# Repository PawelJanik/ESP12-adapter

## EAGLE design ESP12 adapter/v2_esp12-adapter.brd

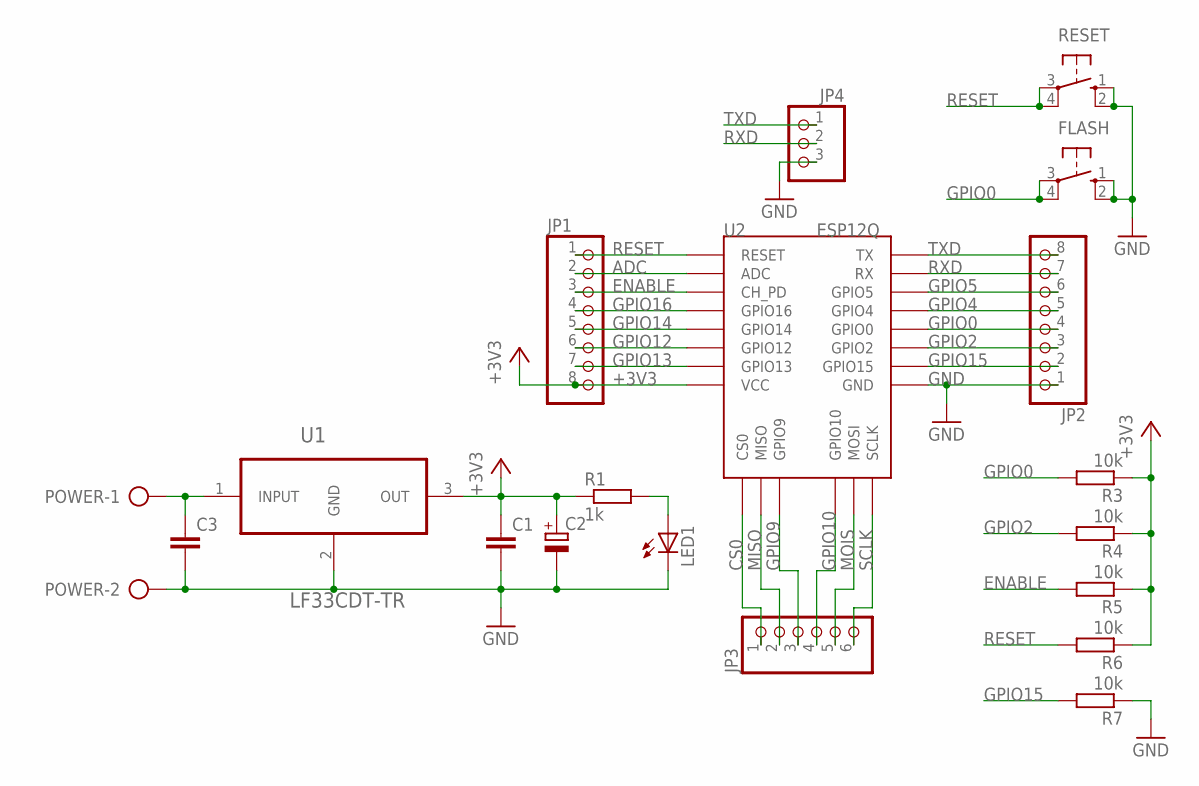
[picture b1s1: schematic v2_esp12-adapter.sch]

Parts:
C1, C3: C-EU025-025X050; C025-025X050
C2: CPOL-EUE2,5-6E; E2,5-6E
FLASH: 10-XX; B3F-10XX
JP1, JP2: PINHD-1X8; 1X08
JP3: PINHD-1X6; 1X06
JP4: PINHD-1X3/90; 1X03/90
LED1: LED5MM
POWER: AK300/2
R1: 1k; R1206
R3, R4, R5, R6, R7: 10k; R1206
RESET: 10-XX; B3F-10XX
U1: LF33CDT-TR; TO228P972X240-3N
U2: ESP12Q

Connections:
+3V3: C1.1, C2.+, JP1.8, R1.1, R3.1, R4.1, R5.1, R6.1, U1.3 (OUT), U2.VCC
ADC: JP1.2, U2.ADC
CS0: JP3.1, U2.CS0
ENABLE: JP1.3, R5.2, U2.CH_PD
GND: C1.2, C2.-, C3.2, FLASH.1 (S), FLASH.2 (S1), JP2.1, JP4.3, LED1.K (C), POWER.2, R7.1, RESET.1 (S), RESET.2 (S1), U1.2 (GND), U2.GND
GPIO0: FLASH.3, FLASH.4 (P1), JP2.4, R3.2, U2.GPIO0
GPIO2: JP2.3, R4.2, U2.GPIO2
GPIO4: JP2.5, U2.GPIO5 (GPIO4)
GPIO5: JP2.6, U2.GPIO4 (GPIO5)
GPIO9: JP3.3, U2.GPIO9
GPIO10: JP3.4, U2.GPIO10
GPIO12: JP1.6, U2.GPIO12
GPIO13: JP1.7, U2.GPIO13
GPIO14: JP1.5, U2.GPIO14
GPIO15: JP2.2, R7.2, U2.GPIO15
GPIO16: JP1.4, U2.GPIO16
MISO: JP3.2, U2.MISO
MOIS: JP3.5, U2.MOSI
unnamed: LED1.A, R1.2
RESET: JP1.1, R6.2, RESET.3, RESET.4 (P1), U2.RESET
RXD: JP2.7, JP4.2, U2.RX
SCLK: JP3.6, U2.SCLK
TXD: JP2.8, JP4.1, U2.TX
V+: C3.1, POWER.1, U1.1 (INPUT)

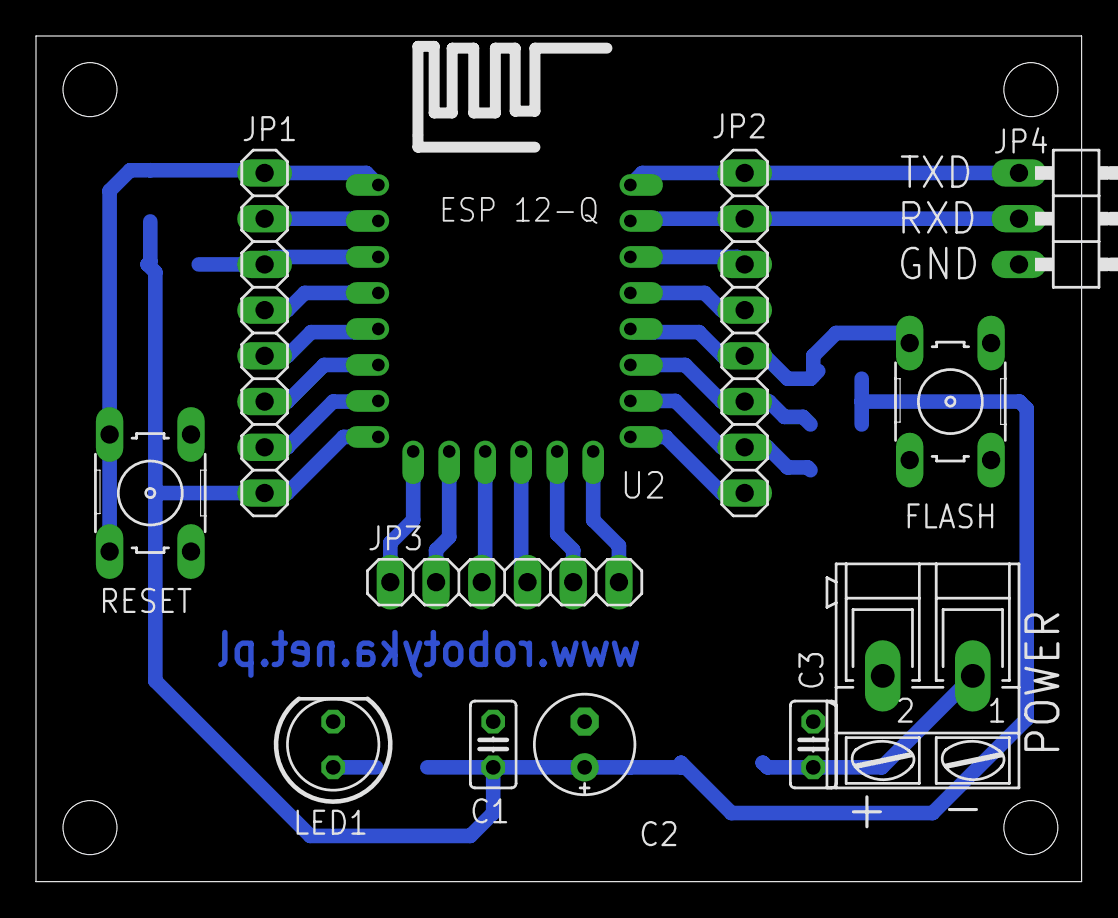
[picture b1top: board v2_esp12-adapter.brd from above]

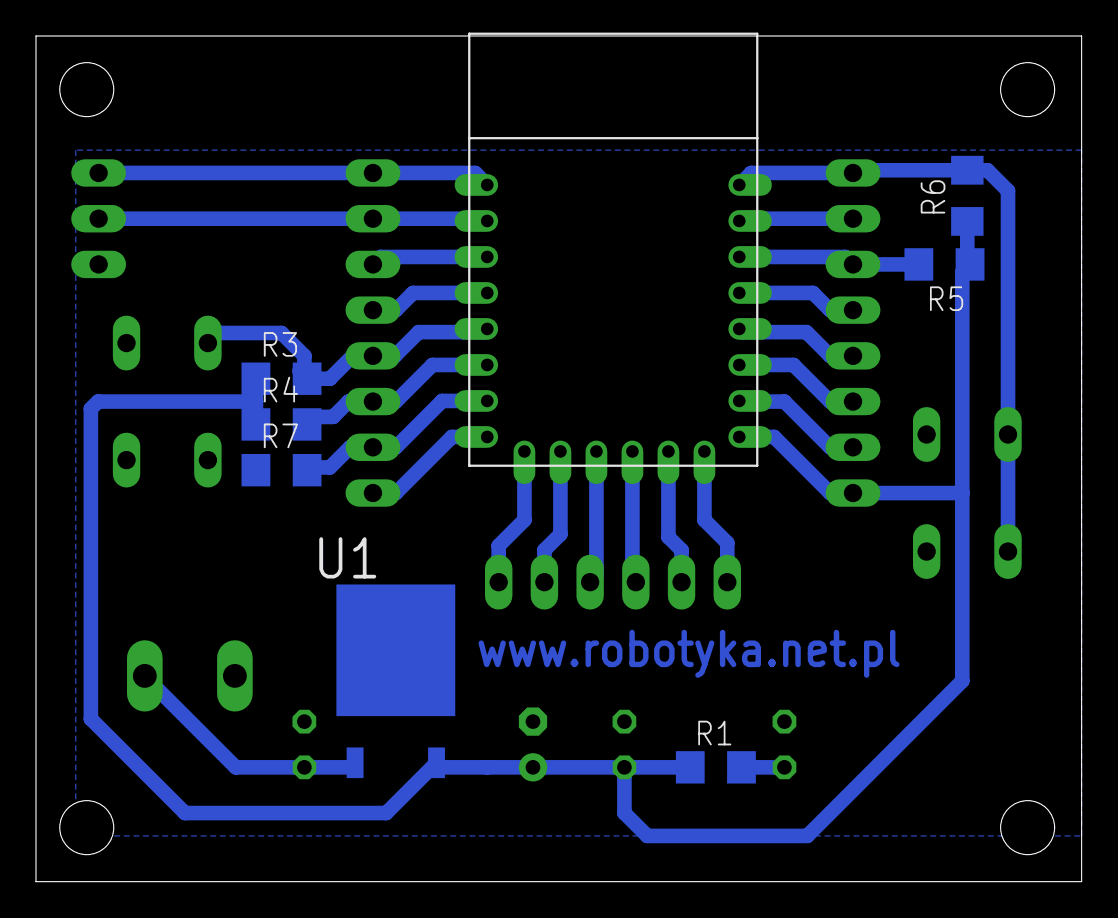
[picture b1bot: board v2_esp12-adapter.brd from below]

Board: 2 copper layers, 58.1 x 47.0 mm, 19 parts (7 on the bottom side), 24 nets.

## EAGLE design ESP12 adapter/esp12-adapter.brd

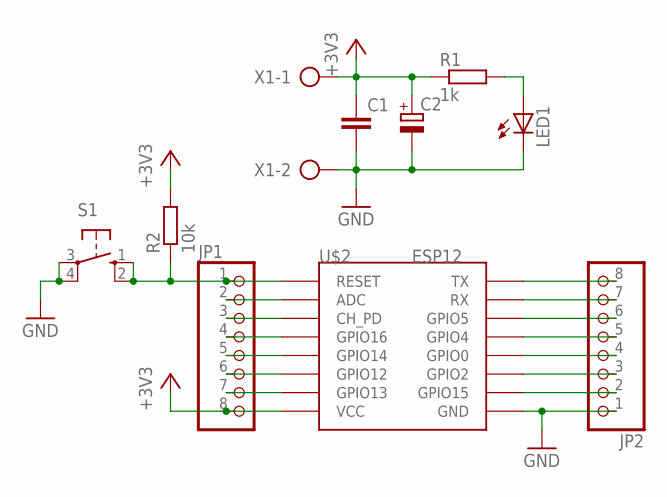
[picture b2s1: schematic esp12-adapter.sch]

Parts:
C1: C-EU025-025X050; C025-025X050
C2: CPOL-EUE3.5-10; E3,5-10
JP1, JP2: PINHD-1X8; 1X08
LED1: LED5MM
R1: 1k; R1206
R2: 10k; R1206
S1: 10-XX; B3F-10XX
U$2: ESP12
X1: AK300/2

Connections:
+3V3: C1.1, C2.+, JP1.8, R1.1, R2.2, U$2.VCC, X1.1
GND: C1.2, C2.-, JP2.1, LED1.K (C), S1.3, S1.4 (P1), U$2.GND, X1.2
unnamed: JP1.1, R2.1, S1.1 (S), S1.2 (S1), U$2.RESET
unnamed: JP1.2, U$2.ADC
unnamed: JP1.3, U$2.CH_PD
unnamed: JP1.4, U$2.GPIO16
unnamed: JP1.5, U$2.GPIO14
unnamed: JP1.6, U$2.GPIO12
unnamed: JP1.7, U$2.GPIO13
unnamed: JP2.8, U$2.TX
unnamed: JP2.7, U$2.RX
unnamed: JP2.6, U$2.GPIO4 (GPIO5)
unnamed: JP2.5, U$2.GPIO5 (GPIO4)
unnamed: JP2.4, U$2.GPIO0
unnamed: JP2.3, U$2.GPIO2
unnamed: JP2.2, U$2.GPIO15
unnamed: LED1.A, R1.2

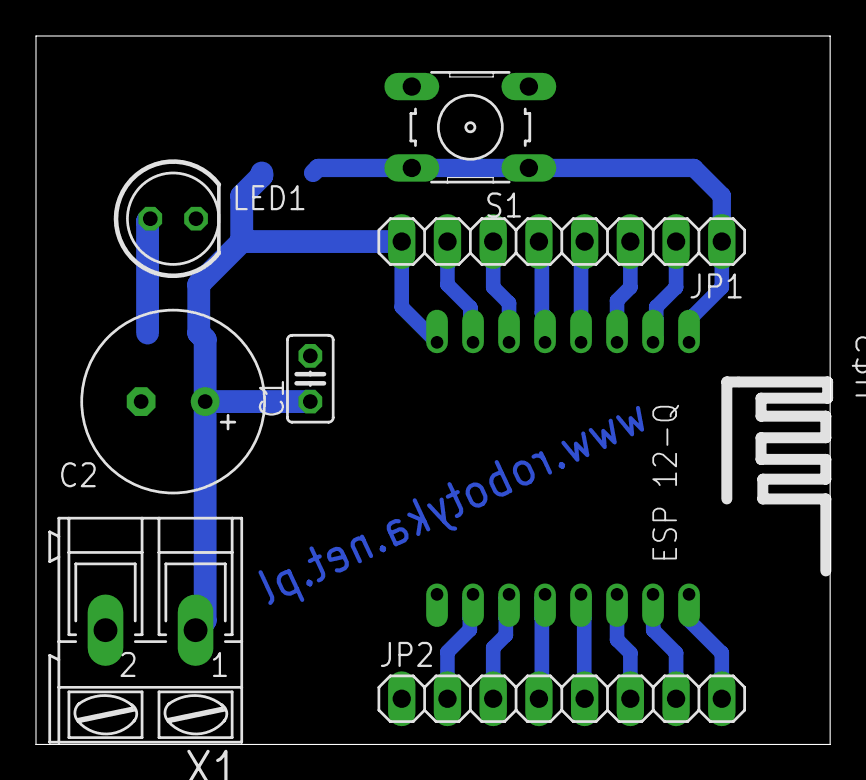
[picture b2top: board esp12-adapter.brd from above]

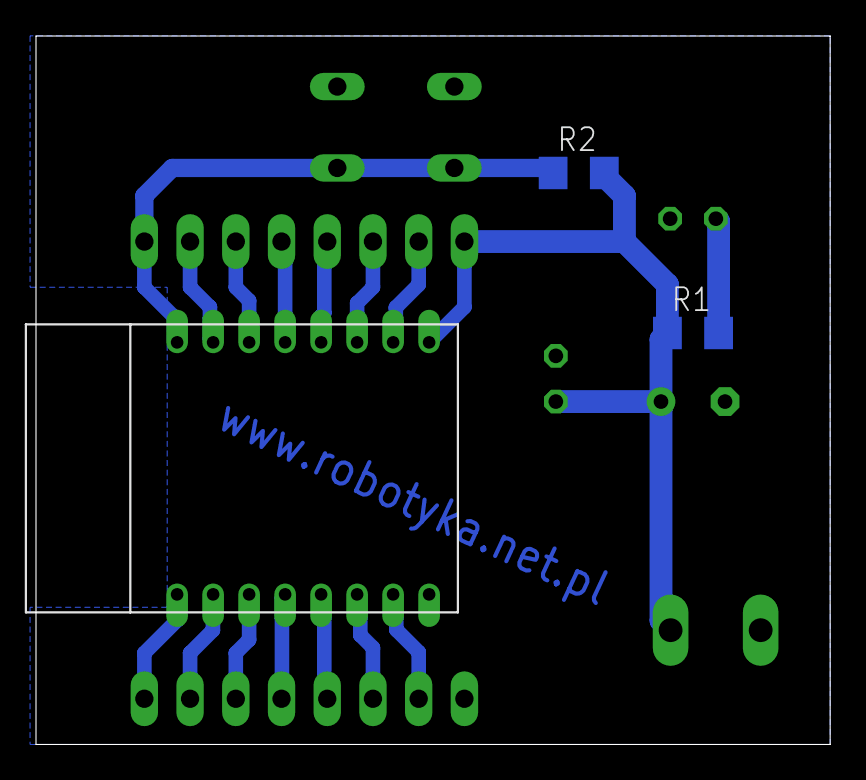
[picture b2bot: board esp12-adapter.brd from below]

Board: 2 copper layers, 44.1 x 39.4 mm, 10 parts (2 on the bottom side), 17 nets.

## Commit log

2018-12-08 Schemat and PCB design
2018-12-08 PDF file
2018-12-22 Second version
2018-12-23 Update tNames layer
